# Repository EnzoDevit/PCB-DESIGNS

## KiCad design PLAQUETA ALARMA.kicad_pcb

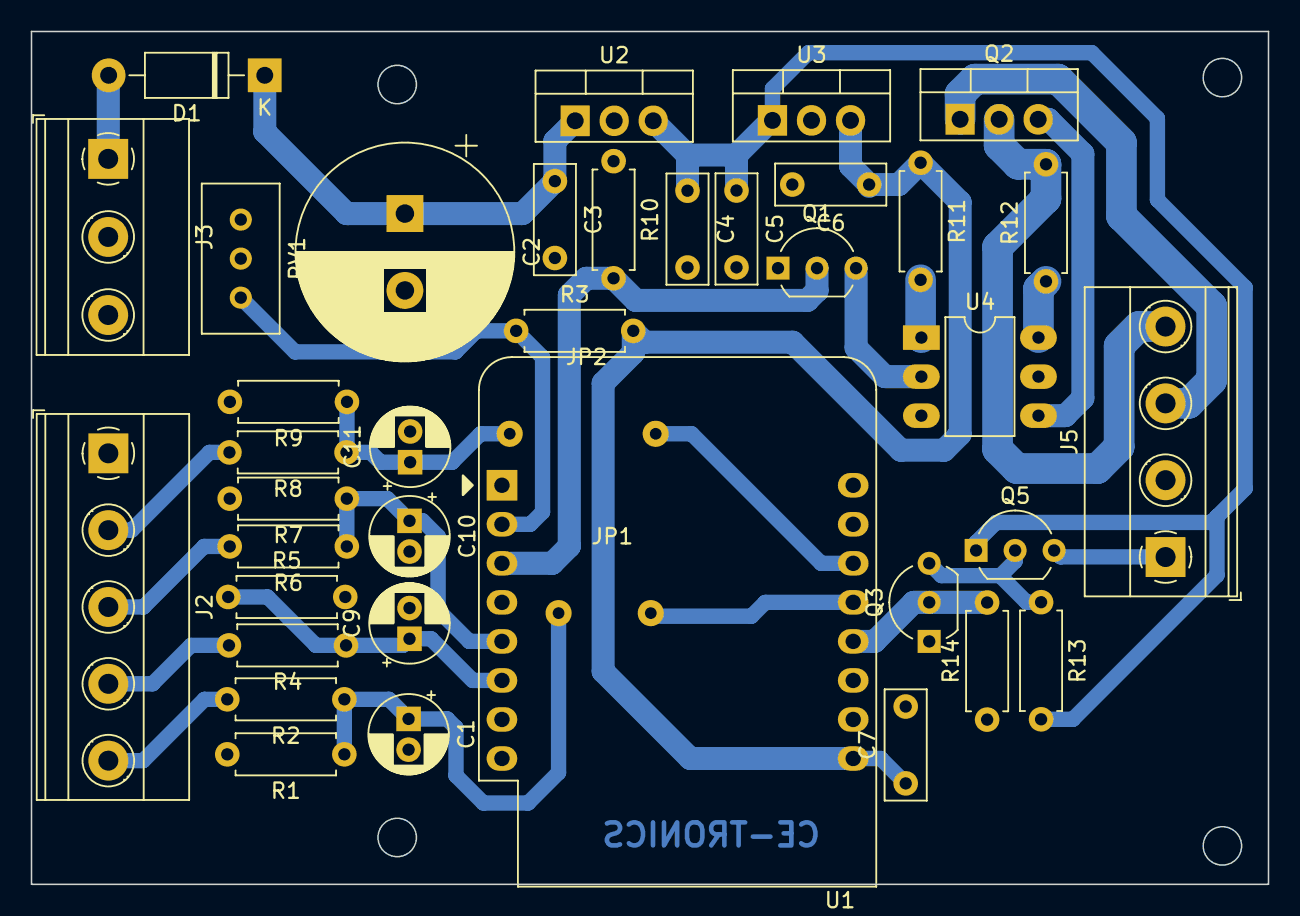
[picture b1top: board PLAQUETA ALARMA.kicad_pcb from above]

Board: 2 copper layers, 80.5 x 55.5 mm, 39 parts (0 on the bottom side), 24 nets.

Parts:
C1, C9, C10, C11: 4.7uf 50v; CP_Radial_D5.0mm_P2.00mm
C2: 1000uF 50v; CP_Radial_D14.0mm_P5.00mm
C3, C4, C5, C6, C7: 104; C_Disc_D7.0mm_W2.5mm_P5.00mm
D1: 1N4007; D_DO-41_SOD81_P10.16mm_Horizontal
J2: bornera 01x05; TerminalBlock_Phoenix_MKDS-1,5-5_1x05_P5.00mm_Horizontal
J3: bornera 01x03; TerminalBlock_Phoenix_MKDS-1,5-3-5.08_1x03_P5.08mm_Horizont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
J5: bornera 01x04; TerminalBlock_Phoenix_MKDS-1,5-4_1x04_P5.00mm_Horizontal
JP1, JP2: Jumper_2_Bridged; JUMPER
Q1, Q3: 2N7000; TO-92_Inline_Wide
Q2: BT138-800; TO-220-3_Vertical
Q5: BC548; TO-92_Inline_Wide
R1, R5, R7, R9, R10, R14: 1M; R_Axial_DIN0207_L6.3mm_D2.5mm_P7.62mm_Horizontal
R2, R4, R6, R8: 1k; R_Axial_DIN0207_L6.3mm_D2.5mm_P7.62mm_Horizontal
R3: 100k; R_Axial_DIN0207_L6.3mm_D2.5mm_P7.62mm_Horizontal
R11, R12: 220R; R_Axial_DIN0207_L6.3mm_D2.5mm_P7.62mm_Horizontal
R13: 220; R_Axial_DIN0207_L6.3mm_D2.5mm_P7.62mm_Horizontal
RV1: preset 100k; Potentiometer_Bourns_3296W_Vertical
U1: WeMos_D1_mini MODULO; WEMOS_D1_mini_light
U2: LM7812_TO220; TO-220-3_Vertical
U3: L7805; TO-220-3_Vertical
U4: MOC3061M; DIP-6_W7.62mm_LongPads

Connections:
12vBuzz: J5.1, Q5.3 (E)
+5V: C6.1, C7.1, R3.2, R11.1, U1.9 (5V), U3.3 (OUT)
+12V: C4.1, C5.1, Q5.1 (C), R13.2, U2.3 (VO), U3.1 (IN)
+12VA: D1.2 (A), J3.1
A0: R3.1, RV1.1, U1.2 (A0)
GND: C1.2, C2.2, C3.2, C4.2, C5.2, C6.2, C7.2, C9.2, C10.2, C11.2, J2.1, J3.3, J5.2, Q1.1 (S), Q3.1 (S), R1.2, R5.2, R7.2, R9.2, R10.1, R14.1, RV1.2, RV1.3, U1.10 (GND), U2.2 (GND), U3.2 (GND)
Llave: J2.2, R8.2
Llave_IN: C11.1, JP2.1 (A), JP2.2 (B), R8.1, R9.1, U1.14 (SCL/D1)
unnamed: C2.1, C3.1, D1.1 (K), U2.1 (VI)
unnamed: Q1.3 (D), U4.2
unnamed: Q2.3 (G), U4.4
unnamed: Q3.3 (D), Q5.2 (B), R13.1
unnamed: R11.2, U4.1
unnamed: R12.1, U4.6
Portero: J2.3, R6.2
Portero_IN: C10.1, R6.1, R7.1, U1.5 (MISO/D6)
Sensor_1: J2.5, R2.2
Sensor_1_IN: C1.1, JP1.1 (A), JP1.2 (B), R1.1, R2.1, U1.13 (SDA/D2)
Sensor_2: J2.4, R4.2
Sensor_2_IN: C9.1, R4.1, R5.1, U1.6 (MOSI/D7)
buzzer: Q3.2 (G), R14.2, U1.12 (D3)
cerrojo: Q1.2 (G), R10.2, U1.3 (D0)
cerrojo1: J5.4, Q2.2 (A2), R12.2
cerrojo2: J5.3, Q2.1 (A1)
